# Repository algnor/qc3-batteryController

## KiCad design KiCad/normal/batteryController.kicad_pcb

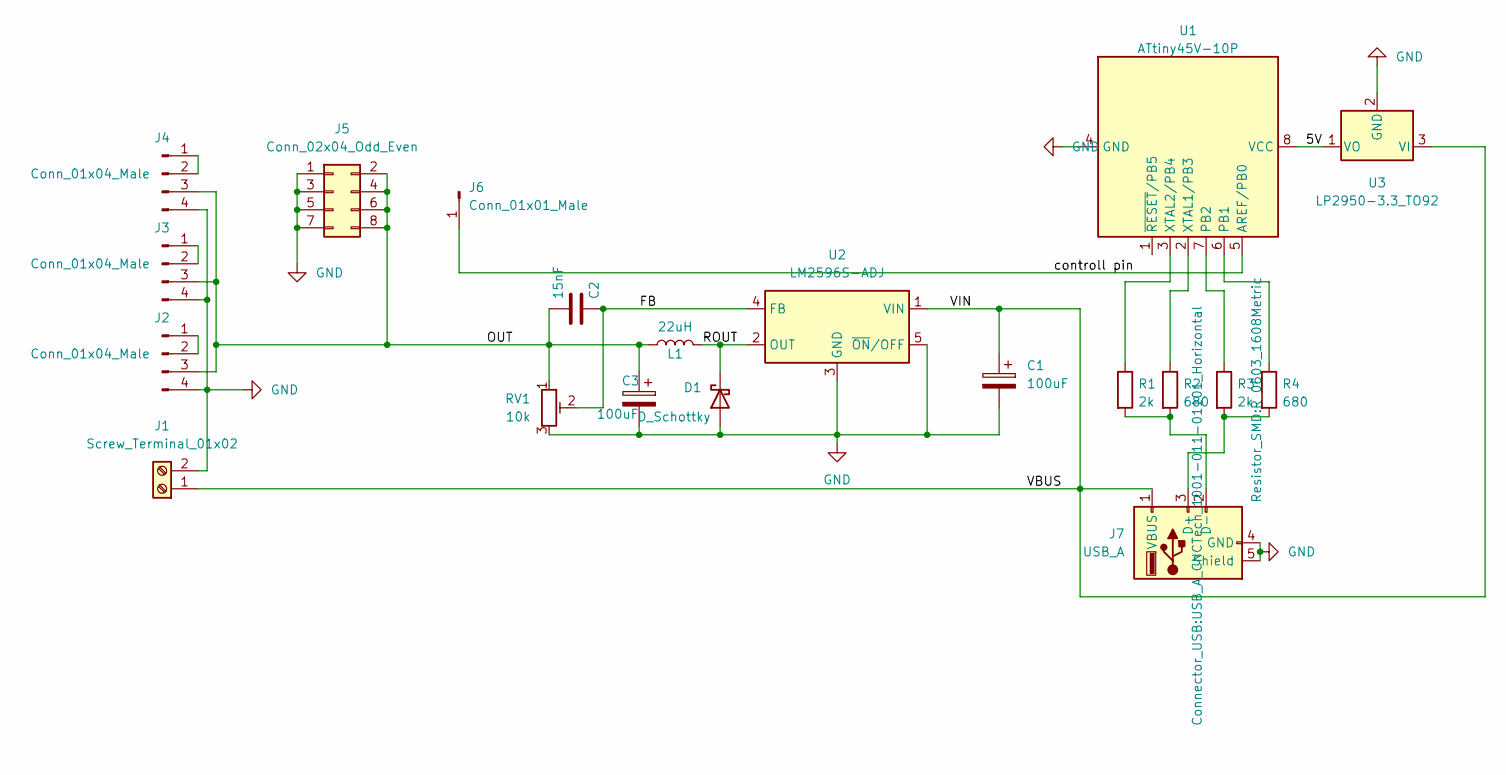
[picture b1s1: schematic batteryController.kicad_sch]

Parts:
C1, C3: 100uF; CP_Radial_D6.3mm_P2.50mm
C2: 15nF; C_Rect_L7.0mm_W2.5mm_P5.00mm
D1: D_Schottky; D_1206_3216Metric
J1: Screw_Terminal_01x02; TerminalBlock_Phoenix_MPT-0,5-2-2.54_1x02_P2.54mm_Horizontal
J2, J3, J4: Conn_01x04_Male; PinHeader_1x04_P2.54mm_Vertical
J5: Conn_02x04_Odd_Even; PinHeader_2x04_P2.54mm_Vertical
J6: Conn_01x01_Male; PinHeader_1x01_P2.54mm_Vertical
J7: USB_A; USB_A_CNCTech_1001-011-01101_Horizontal
L1: 22uH; sdr1006
R1, R3: 2k; R_0603_1608Metric
R2, R4: 680; R_0603_1608Metric
RV1: 10k; Potentiometer_Bourns_3266Y_Vertical
U1: ATtiny45V-10P; DIP-8_W7.62mm_Socket
U2: LM2596S-ADJ; TO-263-5_TabPin3
U3: LP2950-3.3_TO92; SOT-89-3

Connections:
/5V: U1.8 (VCC), U3.1 (VO)
/FB: C2.1, RV1.2, U2.4 (FB)
/OUT: C2.2, C3.1, J2.3, J3.3, J4.3, J5.2, J5.4, J5.6, J5.8, L1.2, RV1.1
/ROUT: D1.1 (K), L1.1, U2.2 (OUT)
/VBUS: C1.1, J1.1, J7.1 (VBUS), U2.1 (VIN), U3.3 (VI)
/controll pin: J6.1, U1.5 (AREF/PB0)
GND: C1.2, C3.2, D1.2 (A), J1.2, J2.4, J3.4, J4.4, J5.1, J5.3, J5.5, J5.7, J7.4 (GND), J7.5 (Shield), RV1.3, U1.4 (GND), U2.3 (GND), U2.5 (~ON/OFF), U3.2 (GND)
unnamed: J2.1, J2.2
unnamed: J3.1, J3.2
unnamed: J4.1, J4.2
unnamed: J7.3 (D+), R3.2, R4.2
unnamed: R1.1, U1.3 (XTAL2/PB4)
unnamed: J7.2 (D-), R1.2, R2.2
unnamed: R2.1, U1.2 (XTAL1/PB3)
unnamed: R3.1, U1.7 (PB2)
unnamed: R4.1, U1.6 (PB1)

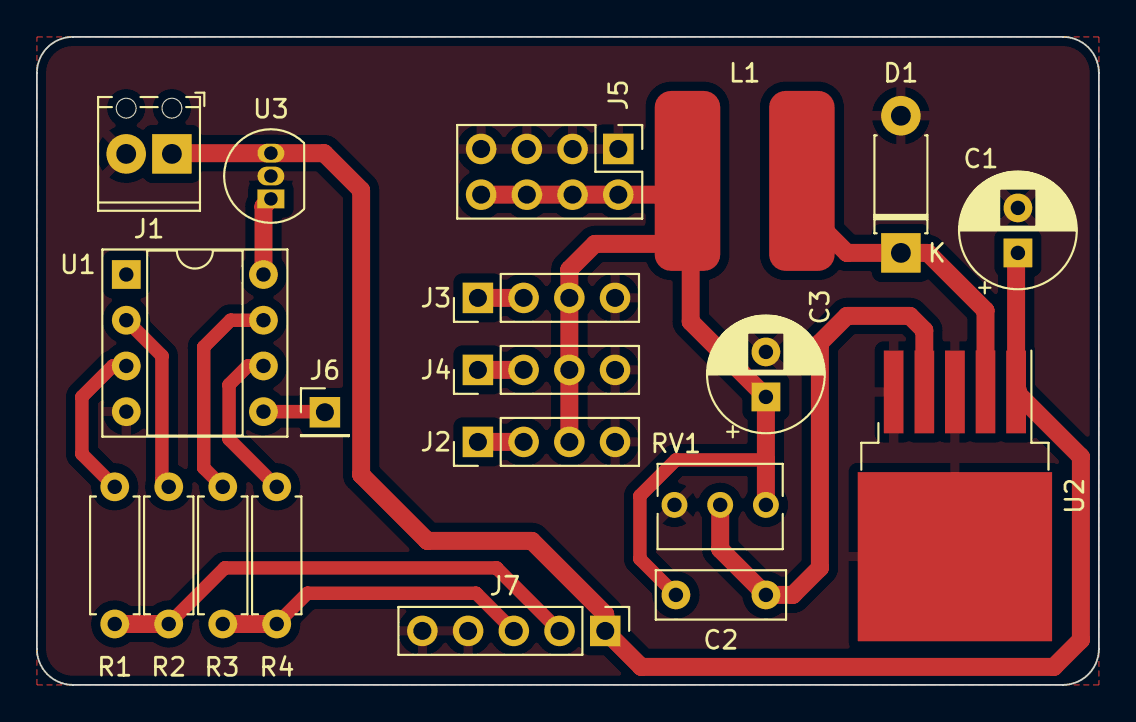
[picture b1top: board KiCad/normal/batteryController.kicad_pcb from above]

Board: 2 copper layers, 59.0 x 36.0 mm, 20 parts (0 on the bottom side), 16 nets.

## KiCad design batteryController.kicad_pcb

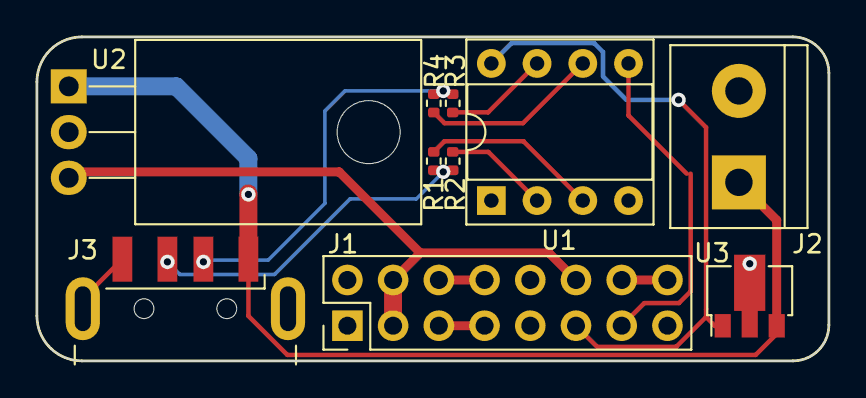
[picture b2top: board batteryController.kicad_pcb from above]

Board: 2 copper layers, 44.0 x 18.0 mm, 10 parts (0 on the bottom side), 14 nets.

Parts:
J1: Conn_02x08_Counter_Clockwise; PinHeader_2x08_P2.54mm_Vertical
J2: Screw_Terminal_01x02; TerminalBlock_bornier-2_P5.08mm
J3: USB_A; USB_A_CNCTech_1001-011-01101_Horizontal
R1, R3: 2k; R_0402_1005Metric
R2, R4: 680; R_0402_1005Metric
U1: ATtiny45V-10P; DIP-8_W7.62mm_Socket
U2: L7806CV; TO-220-3_Horizontal_TabDown
U3: L78L05_SOT89; SOT-89-3

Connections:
/5V: J1.11, U1.8 (VCC), U3.1 (OUT)
/6V: J1.3, J1.4, J1.12, U2.3 (OUT)
/D+: J3.3 (D+), R1.2, R2.2
/D-: J3.2 (D-), R3.2, R4.2
/GND: J1.1, J1.2, J1.9, J1.10, J2.2, J3.4 (GND), J3.5 (Shield), U1.4 (GND), U2.2 (GND), U3.2 (GND)
/VBUS: J2.1, J3.1 (VBUS), U2.1 (IN), U3.3 (IN)
/controll pin: J1.13, U1.5 (AREF/PB0)
unnamed: J1.5, J1.7
unnamed: J1.6, J1.8
unnamed: J1.14, J1.16
unnamed: R1.1, U1.3 (XTAL2/PB4)
unnamed: R2.1, U1.2 (XTAL1/PB3)
unnamed: R3.1, U1.7 (PB2)
unnamed: R4.1, U1.6 (PB1)

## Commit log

2022-03-13 moved to its own repository
2022-03-13 separated hardware and software into different folders
2022-03-13 added software
2022-03-13 Create LICENSE
2022-03-13 added panelization
2022-08-15 redesign to use switching voltage regulator
2022-08-15 changed 5v regulator
2022-08-18 made version using smt components
2022-08-18 spaced out more for pcb milling
2022-08-18 spaced even further out for pcb milling
